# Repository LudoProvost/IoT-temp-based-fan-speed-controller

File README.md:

# Temperature Based Fan Speed Controller on Custom PCB

## Note:
The IoT part of this project has not been completed yet. 

## Components
1. ### ESP8266 NodeMCU
    Used for data processing through GPIO12 and controls fan speed by varying MOSFET gate voltage through GPIO16. 
2. ### LM340 Fixed Voltage Regulator
    Regulated voltage from barrel jack (9-12V) to NodeMCU (3.3-5V).
2. ### DS18B20 Digital Thermometer
    Used to get temperature readings. Using parasite power.
3. ### IRF540 Power MOSFET
    Used to control the fan speed.
4. ### Others
    1. 0.22uF electrolytic capacitor
    2. 0.1uF electrolytic capacitor
    3. Barrel jack connector
    4. 10K resistor
    5. 4.7K resistor

## Schematic

## PCB editor
The KiCad PCD editor was used to design the PCB below. 

3D render of the PCB without a custom footprint for the NodeMCU:

## Datasheets used
1. [ESP8266 NodeMCU](https://handsontec.com/dataspecs/module/esp8266-V13.pdf)
2. [LM340](https://www.ti.com/lit/ds/symlink/lm7800.pdf)
3. [DS18B20](https://mm.digikey.com/Volume0/opasdata/d220001/medias/docus/2890/UMW%20DS18B20.pdf)
4. [IRF540](https://www.vishay.com/docs/91021/irf540.pdf)
5. [Barrel jack connector](https://www.cuidevices.com/product/resource/pj-002a.pdf)

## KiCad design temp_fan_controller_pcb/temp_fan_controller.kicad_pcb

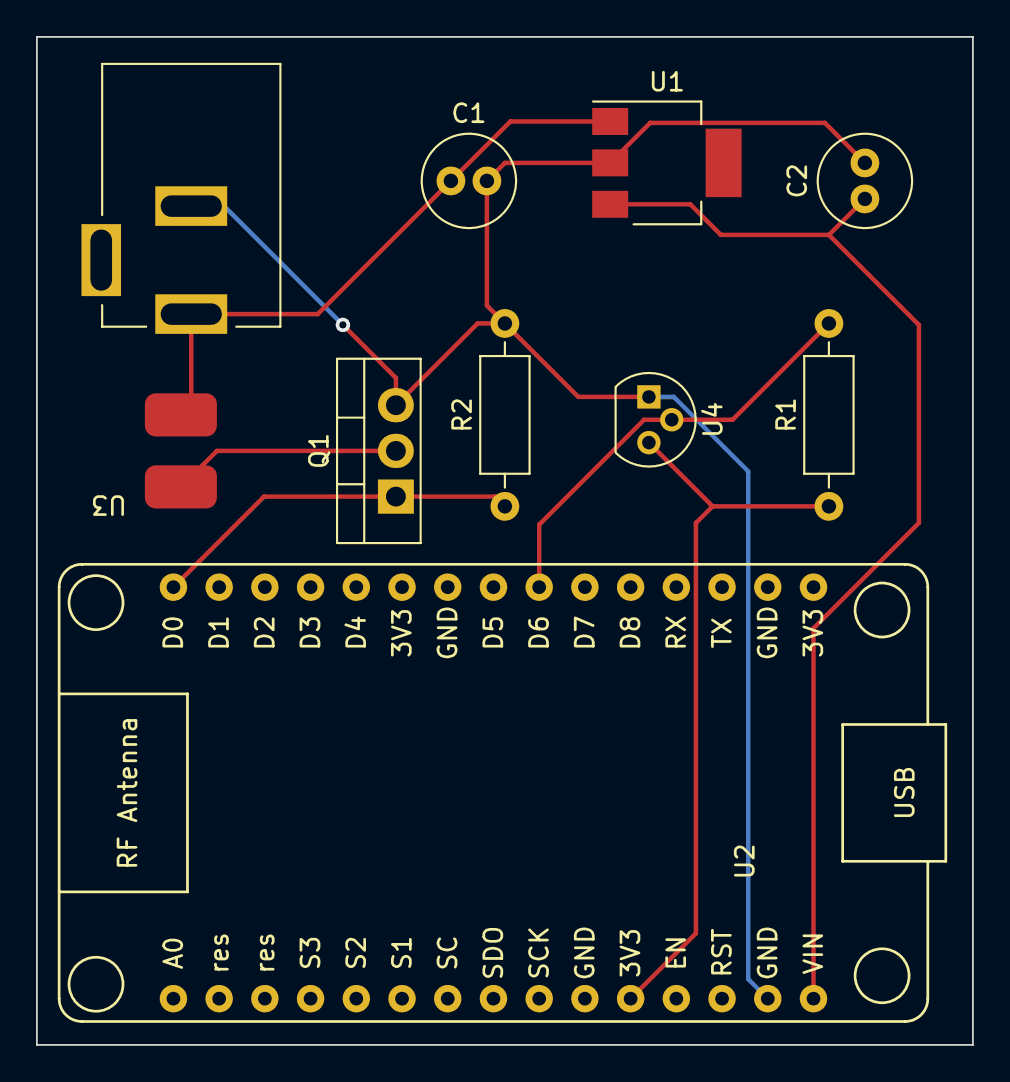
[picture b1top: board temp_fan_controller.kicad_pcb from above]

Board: 2 copper layers, 52.0 x 56.0 mm, 10 parts (0 on the bottom side), 7 nets.

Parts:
Barrel_Jack_Connector1: Barrel_Jack_Switch_Pin3Ring; BarrelJack_G-1005B
C1: 0.22uF; C_Radial_D5.0mm_H11.0mm_P2.00mm
C2: 0.1uF; C_Radial_D5.0mm_H11.0mm_P2.00mm
Q1: IRF540N; TO-220-3_Vertical
R1: 4.7k; R_Axial_DIN0207_L6.3mm_D2.5mm_P10.16mm_Horizontal
R2: 10k; R_Axial_DIN0207_L6.3mm_D2.5mm_P10.16mm_Horizontal
U1: LM340; SOT-223
U2: NodeMCU1.0(ESP-12E); NodeMCU1.0(12-E)
U3: FAN12V
U4: DS18B20; TO-92

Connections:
GND: Barrel_Jack_Connector1.2, C1.2, C2.2, Q1.3 (S), R2.2, U1.2 (GND), U2.14 (GND), U4.1 (GND)
unnamed: Barrel_Jack_Connector1.1, C1.1, U1.1 (VIN), U3.1 (VIN)
unnamed: C2.1, U1.3 (OUT), U2.15 (VIN)
unnamed: Q1.2 (D), U3.2 (GND)
unnamed: R1.1, U2.11 (3.3V), U4.3 (VDD)
unnamed: R1.2, U2.22 (D6(GPIO12)), U4.2 (DQ)
unnamed: Q1.1 (G), R2.1, U2.30 (D0(GPIO16))
